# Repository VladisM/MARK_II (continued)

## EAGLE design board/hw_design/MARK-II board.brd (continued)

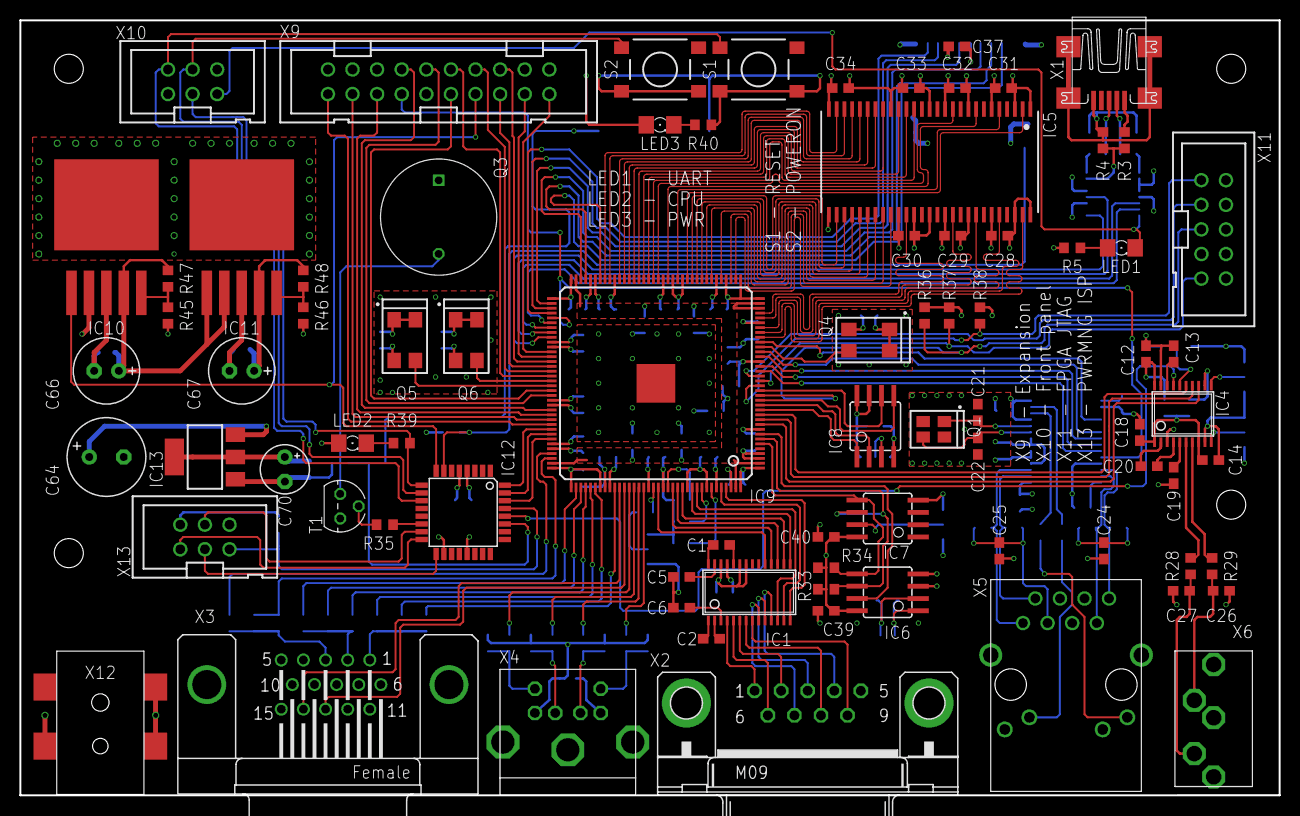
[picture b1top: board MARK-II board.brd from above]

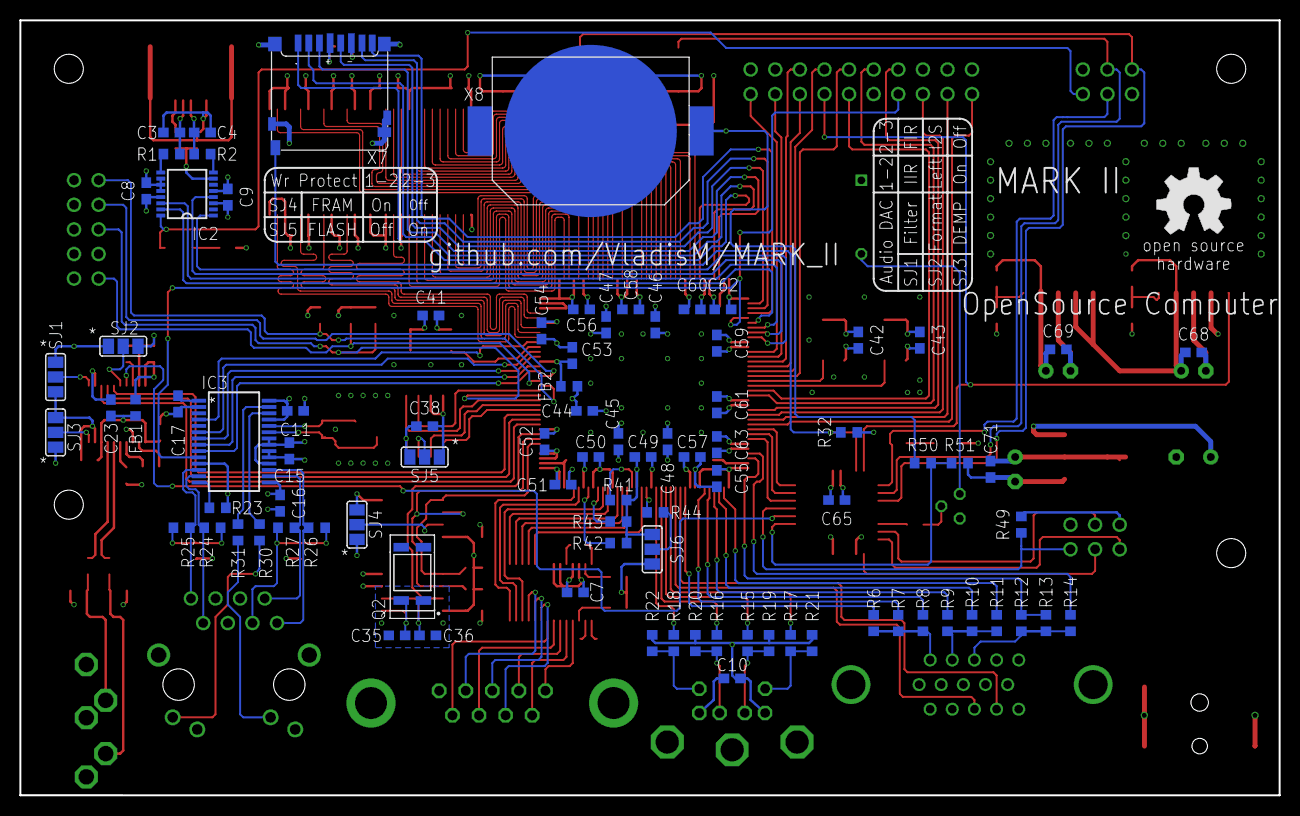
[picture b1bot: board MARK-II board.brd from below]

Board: 4 copper layers, 130.0 x 80.0 mm, 169 parts (89 on the bottom side), 186 nets.

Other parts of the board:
LOGO1: OSHW_8MM

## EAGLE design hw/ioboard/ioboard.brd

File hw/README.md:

In this directory are stored hardware schematics and PSBs related to the MARK_II.

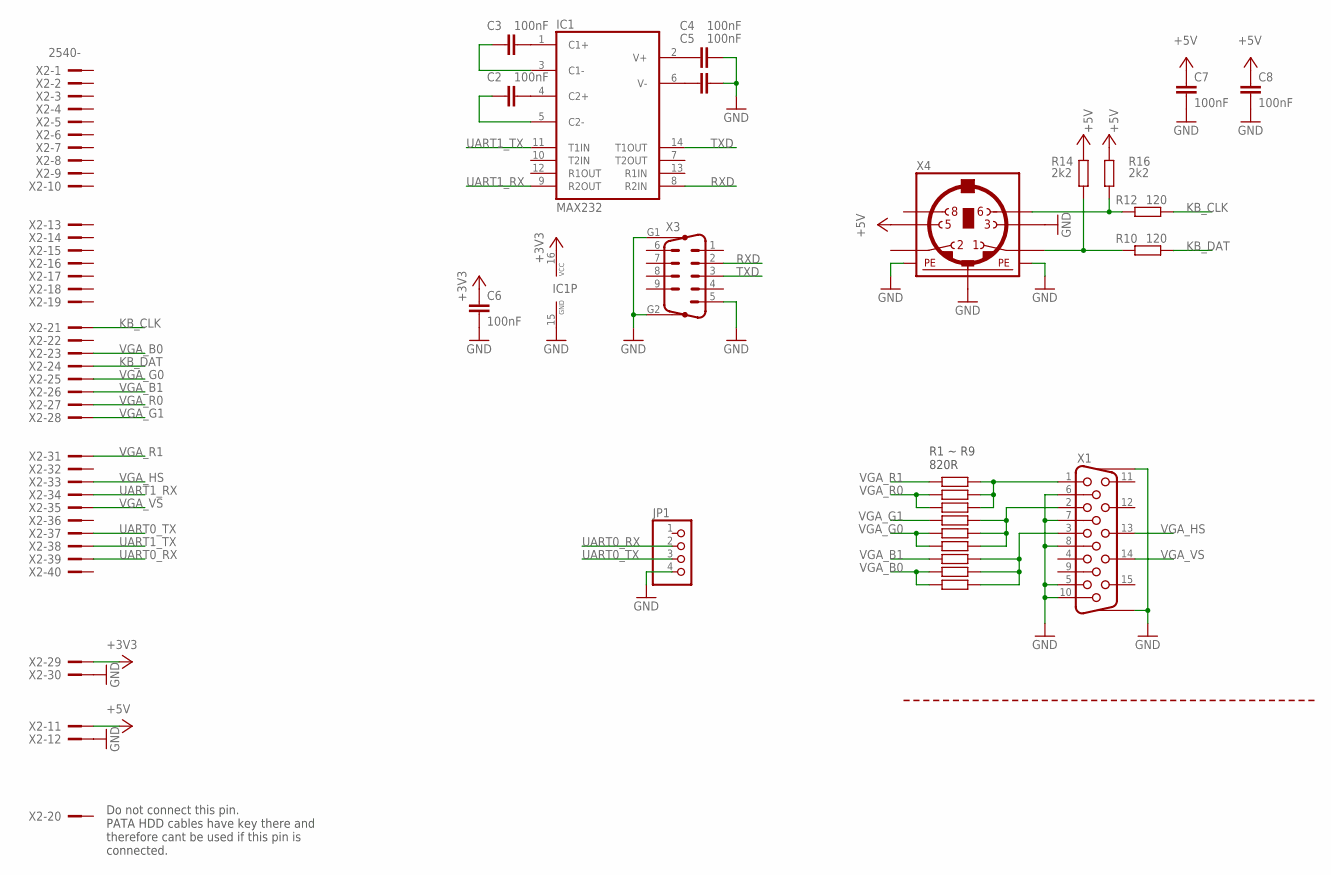
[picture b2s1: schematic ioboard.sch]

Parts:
C2, C3, C4, C5, C6, C7, C8: 100nF; C025-025X050
IC1: MAX232; DIL16
JP1: PINHD-1X4; 1X04
R1, R2, R3, R4, R5, R6, R7, R8, R9: 820; 0204/7
R10, R12: 120; 0204/7
R14, R16: 2k2; 0204/7
X1: HF15H; HDF15H
X2: 2540-; PAK100/2500-40
X3: M09HP
X4: MINI_DIN_6; M_DIN6

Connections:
+3V3: C6.1, IC1.16 (VCC), X2.29
+5V: C7.1, C8.1, R14.2, R16.2, X2.11, X4.5
GND: C4.2, C5.2, C6.2, C7.2, C8.2, IC1.15 (GND), JP1.4, X1.5, X1.6, X1.7, X1.8, X1.10, X1.SCH1, X1.SCH2, X2.12, X2.30, X3.5, X3.G1, X3.G2, X4.3, X4.SH1 (PE1), X4.SH2 (PE2), X4.SH3 (PE3)
KB_CLK: R12.1, X2.21
KB_DAT: R10.1, X2.24
unnamed: R12.2, R16.1, X4.6
unnamed: R10.2, R14.1, X4.1
unnamed: C3.2, IC1.1 (C1+)
unnamed: C2.2, IC1.4 (C2+)
unnamed: C4.1, IC1.2 (V+)
unnamed: R7.1, R8.1, R9.1, X1.3
unnamed: R4.1, R5.1, R6.1, X1.2
unnamed: R1.1, R2.1, R3.1, X1.1
unnamed: C5.1, IC1.6 (V-)
unnamed: C3.1, IC1.3 (C1-)
unnamed: C2.1, IC1.5 (C2-)
RXD: IC1.8 (R2IN), X3.2
TXD: IC1.14 (T1OUT), X3.3
UART0_RX: JP1.2, X2.39
UART0_TX: JP1.3, X2.37
UART1_RX: IC1.9 (R2OUT), X2.34
UART1_TX: IC1.11 (T1IN), X2.38
VGA_B0: R8.2, R9.2, X2.23
VGA_B1: R7.2, X2.26
VGA_G0: R5.2, R6.2, X2.25
VGA_G1: R4.2, X2.28
VGA_HS: X1.13, X2.33
VGA_R0: R2.2, R3.2, X2.27
VGA_R1: R1.2, X2.31
VGA_VS: X1.14, X2.35

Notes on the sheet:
R1 ~ R9 820R
Do not connect this pin. PATA HDD cables have key there and therefore cant be used if this pin is connected.

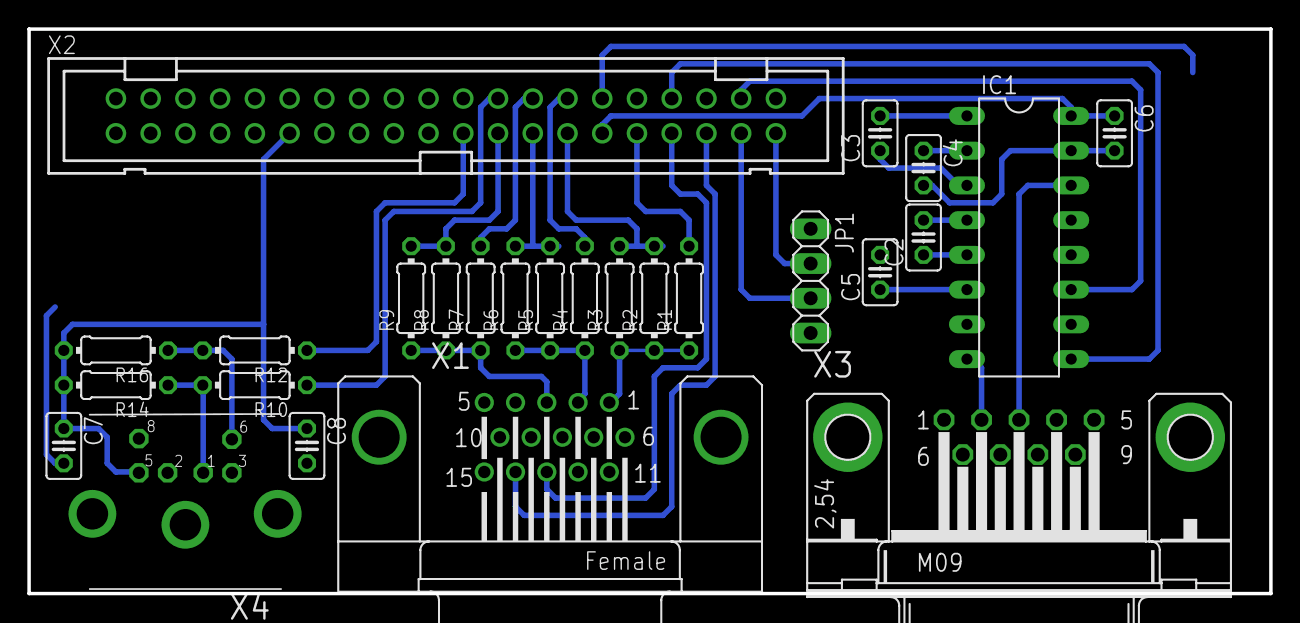
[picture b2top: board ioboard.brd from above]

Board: 2 copper layers, 90.8 x 41.3 mm, 26 parts (0 on the bottom side), 30 nets.

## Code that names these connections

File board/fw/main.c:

#include <stdint.h>

#define F_CPU 1000000UL

#include <avr/io.h>
#include <util/delay.h>
#include <avr/interrupt.h>

/*
 * Macro definitions
 */

#define POWER_ON        PORTB |= (1 << PB7)
#define POWER_OFF       PORTB &= ~(1 << PB7)
#define RESET_HI        PORTD |= (1 << PD2)
#define RESET_LOW       PORTD &= ~(1 << PD2)
#define CPULED_ON       PORTD &= ~(1 << PD5)
#define CPULED_OFF      PORTD |= (1 << PD5)
#define SPEAKER_ON      PORTB |= (1 << PB2)
#define SPEAKER_OFF     PORTB &= ~(1 << PB2)
#define AUDIO_MUTE      PORTC |= (1 << PC5)
#define AUDIO_UNMUTE    PORTC &= ~(1 << PC5)

#define HALT 0
#define RUN 1

#define BTN_PRESS 1
#define BTN_UNPRESS 0

#define SD_INSERTED 1
#define SD_NOT_INSERTED 0

#define CMD_READ_VBAT           0b10000000
#define CMD_BEEP_SHORT          0b10000001
#define CMD_BEEP_LONG           0b10000010
#define CMD_LED_ON              0b10000011
#define CMD_LED_OFF             0b10000100
#define CMD_LED_BLINK_SHORT     0b10000101
#define CMD_LED_BLINK_LONG      0b10000110
#define CMD_POWEROFF            0b10000111
#define CMD_RESET               0b10001000
#define CMD_AUDIO_MUTE          0b10001001
#define CMD_AUDIO_UNMUTE        0b10001010
#define CMD_GET_SD_STATE        0b10001011

/*
 * Function prototypes
 */

void init_peripherals();
uint8_t get_reset_btn();
uint8_t get_power_btn();
uint8_t get_sd_state();
void start_sequence();
void shutdown_sequence();
void reset_sequence();
uint8_t read_vbat();
void exec_command();
void send_byte(uint8_t data);

/*
 * Global variables
 */

static volatile uint8_t cmd_byte = 0;
static volatile uint8_t uart_recieved = 0;
static uint8_t state = HALT;

/*
 * Main program
 */

int main(){
    
    init_peripherals();
    sei();
    
    while(1){
                
        if(state == HALT){

            //check if pwrbtn is pressed; if so go to start sequence
            if(get_power_btn() == BTN_PRESS){
                _delay_ms(100);
                if(get_power_btn() != BTN_PRESS) continue;
                start_sequence();
                state = RUN;
            }
        }

        if(state == RUN){

            //check if pwrbtn is pressed; if so go to shutdown sequence
            if(get_power_btn() == BTN_PRESS){
                _delay_ms(100);
                if(get_power_btn() != BTN_PRESS) continue;
                shutdown_sequence();
                state = HALT;
            }
            
            //if reset btn is pressed then go to reset sequence
            else if(get_reset_btn() == BTN_PRESS){
                _delay_ms(100);
                if(get_reset_btn() != BTN_PRESS) continue;
                reset_sequence();
            }
            
            //else, check for task from uart interface
            else if(uart_recieved != 0){
                uart_recieved = 0;
                exec_command();
            }
        }
    }
    return 0;
}

/*
 * ISR vectors
 */

ISR(USART_RX_vect){
    //interrupt from UART
    cmd_byte = UDR0;
    uart_recieved = 1;
}

/*
 * Functions definitions
 */

void init_peripherals(){

    /*
     * Port B configuration
     *
     * PB7  out     power_on
     * PB6  in      sd_sw
     * PB5          ISP
     * PB4          ISP
     * PB3          ISP
     * PB2  out     speaker
     * PB1          nc
     * PB0          nc
     */

    DDRB = 0;
    DDRB |= (1 << PB7) | (1 << PB2);

    /*
     * Port C configuration
     *
     * PC6          reset
     * PC5  out     audio_mute
     * PC4  in      Vbat_voltage (ADC)
     * PC3          nc
     * PC2          nc
     * PC1          nc
     * PC0          nc
     */

    DDRC = 0;
    DDRC |= (1 << PC5);

    /*
     * Port D configuration
     *
     * PD7  in      reset_btn       pullup
     * PD6  in      power_btn       pullup
     * PD5  out     cpu_led
     * PD4          nc
     * PD3          nc
     * PD2  out     pwrmng_res
     * PD1          uart
     * PD0          uart
     */

    DDRD = 0;
    DDRD |= (1 << PD5) | (1 << PD2);
    PORTD |= (1 << PD7) | (1 << PD6);

    /*
     * ADC configuration
     *
     * ADMUX register
     *  VREF = AVcc
     *  result left adjusted
     *  MUX = ADC4
     * 
     * ADCSRA register
     *  enable adc
     *  prescaler = 8
     * 
     * ADCSRB register
     *  default state
     * 
     * DIDR0 register
     *  disable PC4
     */
         
    ADMUX |= (1 << MUX2) | (1 << ADLAR) | (1 << REFS0);
    ADCSRA |= (1 << ADEN) | (1 << ADPS1) | (1 << ADPS0);
    DIDR0 |= (1 << ADC4D);

    /*
     * UART configuration
     *
     * 8N1 4800baud
     * Enable RX interrupt, reciever and transmitter
     */
    
    UBRR0 = 12;
    UCSR0B |= (1 << RXCIE0) | (1 << RXEN0) | (1 << TXEN0); 

    /*
     * Set control pins defaults
     */

    POWER_OFF;
    AUDIO_UNMUTE;
    RESET_LOW;
    CPULED_OFF;
    SPEAKER_OFF;
}

uint8_t get_reset_btn(){
    return !((PIND & (1 << PD7)) >> PD7);
}

uint8_t get_power_btn(){
    return !((PIND & (1 << PD6)) >> PD6);
}

uint8_t get_sd_state(){
    return !((PINB & (1 << PB6)) >> PB6);
}

void start_sequence(){
    //enable voltage regulators and wait a bit
    POWER_ON;
    _delay_ms(5);

    //disable audio output, set reset state
    AUDIO_MUTE;
    RESET_HI;

    //light on LED and produce beep for short while
    CPULED_ON;
    SPEAKER_ON;
    _delay_ms(100);
    SPEAKER_OFF;
    _delay_ms(100);
    CPULED_OFF;

    //wait another while and then unset reset; MARK-II now can run
    _delay_ms(100);
    RESET_LOW;
}

void shutdown_sequence(){
    //light on LED and produce beep for short while
    CPULED_ON;
    SPEAKER_ON;
    _delay_ms(100);
    SPEAKER_OFF;
    _delay_ms(100);
    CPULED_OFF;

    //unmute audio, set reset to low
    AUDIO_UNMUTE;
    RESET_LOW;

    //wait a bit and disable voltage regulatos
    _delay_ms(10);
    POWER_OFF;
}

void reset_sequence(){
    CPULED_ON;
    SPEAKER_ON;
    RESET_HI;
    _delay_ms(100);
    SPEAKER_OFF;
    _delay_ms(100);
    RESET_LOW;
    CPULED_OFF;
}

uint8_t read_vbat(){
    //start single conversion and return ADCH value 
    ADCSRA |= (1 << ADSC);  
    while( ADCSRA & (1 << ADSC) );
    return ADCH;
}

void exec_command(){
    switch(cmd_byte){
        case CMD_READ_VBAT:
            send_byte(read_vbat());
            break;
        case CMD_BEEP_SHORT:
            SPEAKER_ON;
            _delay_ms(100);
            SPEAKER_OFF;
            _delay_ms(100);
            break;
        case CMD_BEEP_LONG:
            SPEAKER_ON;
            _delay_ms(300);
            SPEAKER_OFF;
            _delay_ms(100);
            break;
        case CMD_LED_ON:
            CPULED_ON;
            break;
        case CMD_LED_OFF:
            CPULED_OFF;
            break;
        case CMD_LED_BLINK_SHORT:
            CPULED_ON;
            _delay_ms(100);
            CPULED_OFF;
            _delay_ms(100);
            break;
        case CMD_LED_BLINK_LONG:
            CPULED_ON;
            _delay_ms(300);
            CPULED_OFF;
            _delay_ms(100);
            break;
        case CMD_POWEROFF:
            state = HALT;
            shutdown_sequence();
            break;
        case CMD_RESET:
            reset_sequence();
            break;
        case CMD_AUDIO_MUTE:
            AUDIO_MUTE;
            break;
        case CMD_AUDIO_UNMUTE:
            AUDIO_UNMUTE;           
            break;
        case CMD_GET_SD_STATE:
            send_byte(get_sd_state());
            break;
        default:
            break;
    }
}

void send_byte(uint8_t data){
    while ( !(UCSR0A & (1<<UDRE0)) );
    UDR0 = data;
}

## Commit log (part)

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2016-11-08 Init
    initial version
2016-11-09 fix DEC instruction
    Fix bug in the ALU, instruction DEC now working as should.
2016-11-09 MVIL & MVIH
    Changed behaves of the instruction MVIH and MVIL, now they are loading
    into register only 16b constant. It is easier to write and read this
    instruction in source code.
2016-11-10 CALL
    Fixed CALL instruction, there was wrong microinstructions execution
    order.
2016-11-10 INT accept
    Fixed issue #1. Signal int_accept is synchronous now.
2016-11-24 remove debug signals
2016-11-24 change to 16bit wide address bus
2016-11-24 new test rom
2016-11-29 ISA update
    update format of instruction to use 20b long address
2016-11-29 change ID to implement new ISA
2016-11-29 new rom.mif compiled with new assembler
2016-11-29 gpio ports are more generic and smaller as default
2016-12-29 clean
2016-12-29 Fixed MVIL and MVIH instructions
2016-12-30 Add source for interrupt controller
    Controller have 32 independent interrupt sources with priorities.
    Interrupts are also maskable.
2016-12-30 Add 32 interrupt sources
2017-01-01 Add doc
2017-01-01 Rename CPU-Architecture.md to cpu_architecture.md
2017-01-01 Rename Tools.md to tools.md
2017-01-01 Set theme jekyll-theme-cayman
2017-01-01 Set theme jekyll-theme-slate
2017-01-07 add baudrate generator for uart
2017-01-07 add transmitter for uart
2017-01-10 add reciever code
2017-01-10 add base for uart
    also s few changes in reciever and baudgen, there is no bus interface
    for uart yet
2017-01-10 forgoten dedicated clock for uart
2017-01-10 small fixes
2017-01-17 fix interrupt vectors
2017-01-17 add source
2017-01-17 add system timer
2017-01-30 little fixes
2017-01-30 fix branching
2017-01-31 changed if statements
2017-02-01 fixed uart
2017-02-14 Added VGA driver and Pll
2017-02-23 external sram; ported for DE2 board
    Also added colors for VGA, fixed ack and few instructions...
2017-04-07 Ported to DE0 Nano, add new assembler and linker
    This is large commit. Whole source is ported into DE0 Nano, this is
    finall board to run MARK-II. There is example project for Quartus
    13.0 sp1. Few examples in assembler are also added. VGA driver now
    support more collors. Exsram was deleted, there is small ram from
    M9K block that Cyclone IV have. This RAM is temporary and will be
    replaced with SDRAM.
2017-04-07 deleted forgoten *.pyc
2017-04-07 Added license
2017-04-10 add support for macro parameters
2017-04-10 argument count control in macro
2017-04-11 add io board for DE0 Nano
2017-04-11 Add operand type control in EXPORT and IMPORT pseudo op
2017-04-11 add MVIA instruction into CPU
2017-04-12 Add support for MVIA into assembler
2017-04-12 fix mvia in id
2017-04-12 add gitattributes
2017-04-18 Initial version of emulator
    ram, rom and gpio is working, cpu is also working but not all is tested
2017-04-19 Improved emulator. Add support for system timer and interrupts.
2017-04-25 uart support
2017-04-26 Simplify systim and remove gpio
    SysTimer is simplified by removing timer, no you have to call systim.tick()
    every time when SoC ticks.
    Emulatorion of GPIO is useless, so GPIO is removed.
2017-04-26 Removed timer from MARK-II. Now, tick() is called manualy. Simplified reseting.
2017-04-26 Improved CLI.
2017-04-26 Small fix in usage texts.
2017-04-26 Remove unused rom.eif in emulator and add example of uart loop
2017-04-26 Fix opcode in MVIA
2017-04-27 fix bug in uart created when I fix bug in uart
2017-04-29 add junk folder into gitignore
2017-05-03 improved MVI pseudoop
2017-05-09 rewrite without using pygubu
2017-05-10 add memory view
2017-05-10 merged gui and cli emulators; fix link in assembler help
2017-05-11 first version of disassembler
2017-05-14 disassembler added into emulator
2017-05-14 Updated todo list
2017-05-16 remove eif format; emulator and disasm now use mif insteat
2017-05-16 ldm2mif now use mif library
2017-05-17 fix bug with disasm in gui emul
2017-05-26 add loader code
2017-05-26 change default rom0 mif for bootloader
2017-05-26 Add new structure into README
2017-05-26 fix help messages in case of unrecognized option
2017-06-01 fixed labels in macros (issue #3)
    Labels in macros now work as should.
2017-06-01 new tools version
2017-06-17 emulator gui is now updating when "run to"
2017-06-17 add sync code into loader
2017-06-17 add support for sync into loader PC code
2017-06-19 update code; add 0xBB response after every byte
2017-06-19 add chnages into loader pc code
2017-06-21 add checkbuttons for enable updating regs and mems while 'run to'
2017-06-21 add force exit button from 'run to'
2017-07-06 doc init
2017-07-06 add old peripherals test programs
2017-07-08 add list of tables, MARK-II sys arch image
2017-07-09 Add chapter "System overview".
2017-07-10 Add section 'Core Architecture'
2017-07-10 Add base of peripherals section
2017-07-10 small changes in emul help text
2017-07-10 Change structure of refman; simplify makefile
2017-07-12 Add code of stdio lib written in assembler
2017-07-12 Add rom and ram info; fix spelling mistakes.
2017-07-12 Add gpio section
2017-07-13 Add lstlisting syntax format for MARKII
2017-07-13 add int_driver section
2017-07-13 add chapter about systim, changes in uart and int_driver chapters
2017-07-13 small bug fix
2017-07-13 add chapter about timers
2017-07-13 changed license notice
2017-07-13 Add chapter about ps2, removed GPIO image
2017-07-14 add vga chapter, removed watermark
2017-07-14 Changes in readme and change structure of m2tools
2017-07-14 Clean up in /sw/
2017-07-14 Added missed symlink
2017-07-17 Add missing argument to loader for connecting to emulator.
2017-07-17 New version of IO board - fix issue #2 but remove SD card and ethernet ... not need at this time anyway
2017-07-18 Removed useless code from stdio lib
2017-07-24 Fix issue #4
2017-08-22 Small fix in error message
2017-08-22 Add vbcc source with MARK-II backend
2017-08-24 Add vbcc chapter into refman
2017-08-25 Update uart core
2017-08-25 Speed up working with static and extern variables
2017-08-25 Add doc for new UART core
2017-08-29 Fixed some bugs
2017-08-29 fix another bug
2017-08-29 fix another stupid bug
2017-08-30 Fix in refman
2017-08-31 loader fixed
2017-09-02 fix issue #6; fix bug in vbcc
2017-09-04 Add base of peripheral lib; small change in refman
2017-09-06 Finalize SPL
2017-09-06 Fixed .gitignore
2017-09-06 Add blink example; moved tools into toolchain dir
2017-09-06 Fixed makefile
2017-09-06 Add doxygen into spl
2017-09-07 Add SPL info into refman
2017-09-08 Significantly improved work with blink example.
2017-09-08 Fix makefile
2017-09-08 This commit will fix some issues with vbcc.
    compiler is now able compile vga spl example.
    Added small macro for MULT instruction that is not
    implemented yet in HW
    Finished loading into register and storing from register
    for all types of objects
2017-09-09 Add uart example; NOT TESTED!
2017-09-10 Fixed uart example and improve&fix vbcc
    vbcc changes:
    optimalize assign IC
    lying to vbcc about byte size of all types (this fix bug in addressing arrays)
    optimize loading constants
    fix aligment in emiting OR instruction
    add LSHIFT and RSHIFT macro
2017-09-10 Fix one bug in vga; still vga example not work
2017-09-10 fix bug in colors names
2017-09-11 Improved VRAM0 macro; small optimalizations in compiler
2017-09-11 Finalize SPL examples
    - remove timer example (it is pretty useless without interrupt support in vbcc)
    - add comments into sources
    - add readme
2017-09-11 Change vbcc to version 0.9f
2017-09-11 add barrel shifter source
2017-09-12 Add source of the new regfile; allow arch with 3 internal busses
2017-09-12 Part of new cpu
2017-09-13 create new diagram of instruction decoder
2017-09-14 Add some features to speed up CPU; completed id.dia
2017-09-16 Finalize ID; compilation passed
2017-09-17 ISA changed a bit; Fmax raised but still < 80MHz
2017-09-18 Changed CPU to new architecture
    remove tristate buffers inside CPU
    simplify ID
    new CPU core without tristate buffers
2017-09-18 Work fine with 50MHz
2017-09-19 Add source of new int controler
2017-09-19 Merged fpadd and fpsub; slow down to 40MHz
2017-09-19 changed memory layout
2017-09-20 Fixed layout
2017-09-20 Add ISA document
2017-09-20 Finalize refman; deleted ISA manual - it is part of refman
2017-09-20 Updated SPL
2017-09-20 Updated loader
2017-09-21 Update assembler and refman
    Assembler now support new instructions and new isntruction format
    deleted MOV instruction from refman; CPU doesn't have MOV anymore
2017-09-21 Update loader and stdlibc
2017-09-25 update disassembler to new ISA
2017-09-25 update ldm2mif to new ISA
2017-09-25 Update emulator
    Basic test are done and some bugs are fixed; still need more tests
2017-09-25 Add shifts and mul, rem, div in vbcc
2017-09-25 replace MOV instruction with OR
2017-09-25 Improve negative numbers
2017-09-25 Add support for inline assembler
2017-09-26 Add support for floats; speed-up calls
2017-09-26 Fixed bug in linker
2017-09-27 Fix instruction decoder; improve makefiles in sw/*
2017-09-27 Add disasm into ignore
2017-09-27 fix LDI instruction problem
2017-09-27 Improve disasm output format
2017-09-29 Add info about inline assembler and interrupts
2017-09-29 Add status bar into loader
2017-09-29 Add better version numbering in m2tools
2017-09-29 Add better version number into vbcc backend too.
2017-09-29 Fix nested conditional compilation in assembler
2017-09-30 Speed up to 50MHz
2017-09-30 Speed up to 63MHz
2017-10-02 Update clock generation; set 50MHz
2017-10-02 Edit projet tcl
2017-10-03 Fix bug in backend
2017-10-03 Fix ignore
2017-10-05 Fix bug in video RAM
2017-10-05 Fix linking bug and bug in DS pseudoinstruction
2017-10-05 fix one bug
2017-10-06 Linker is completed
2017-10-06 fix bug; tested working
2017-10-06 Add some files and dir into make clean
2017-10-10 Add sdram driver files
2017-10-10 Set uart clk to 38.4MHz
2017-10-10 Add secret instruction
2017-10-10 Add 30 degree phase offset to sdram clk .. look like it help
2017-10-11 Changed loader baudrate to 9600
2017-10-11 Changed constant in uart example
2017-10-11 Add cursor
2017-10-11 Add new macros for cursor in SPL
    Also delete one comment (it was wrong anyway)
2017-10-16 Add swi example
2017-10-26 Cleanup fpga project
2017-10-28 Fix typo in tcl
2017-10-29 Update spl
    Add vgaio module that allow one to write on VGA in console manner
    Fix toolchain install script
2017-10-31 fix some bugs
2017-11-02 Fix vbcc backend
2017-11-18 Add SDRAM driver
2017-11-20 Add sdram into spl
2017-11-20 Update refman
2017-11-22 moved all examples into SDRAM
2017-11-25 bugfix
2018-01-19 Add initial version of board
2018-01-19 Fix attributes
2018-02-01 Small name changes to better suits HDL files
2018-02-06 Fix clk for pll
2018-02-14 Fixed pwrmng uart connection
2018-04-04 Add ferrite beads
2018-04-07 Fixed some mistakes in component names
2018-04-07 Add settings for FT230X
2018-04-10 Changed LDO
2018-04-11 Update firmware for pwrmng
2018-04-11 Changed instruction decoder diagram
2018-04-13 Fix bugs in pwrmng fw; tested and is working
2018-04-14 Remove old HDL code
2018-04-15 Add micro SD detect function
2018-04-16 Add pwrmng library
2018-04-16 Fixed VGA
2018-04-18 Fixed SDRAM
2018-04-19 update rest of doc
2018-04-19 Update readme, gitignore and gitattribute
2018-04-25 add timer hdl code
2018-04-26 Add timer into SPL
2018-04-26 SPL was divided into two parts 1-SPL 2-BSP
2018-05-01 bugfix in SPL
2018-05-01 add timer example
2018-05-02 Fixed timer example
2018-05-23 add doc and spl
2018-05-23 Typo mistake
2018-05-24 Fix array pointer bug
2018-05-24 Add multiple export check
2018-06-01 Low level optimalizations in loader
2018-06-03 Remove pipe from sdram dcfifos
